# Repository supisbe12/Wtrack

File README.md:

# Wtrack
Wtrack — a multi-network location tracker device

Wtrack is a tracker with a combination of Apple Find My, Hubble (terrestrial + satellite), GPS, and BLE proximity detection on one barebones PCB (no enclosure) which goes inside your wallet.
I want it to be barebone because I wanted to be able to see the actual PCB because it looks cool ,But I am planning to add a layer acrylic spray that I already have available to prevent water from affecting the board.

---
Schematic

PCB

3D view

Battery Cap

---
Bill Of Materials: https://docs.google.com/spreadsheets/d/1D9NDHI8oiGVwoLBUYLz9mFe_7Vkk39w_oN8q6zxxxLU/edit?usp=sharing

Bill of materials (CSV): https://github.com/supisbe12/Wtrack/blob/main/BOM.csv

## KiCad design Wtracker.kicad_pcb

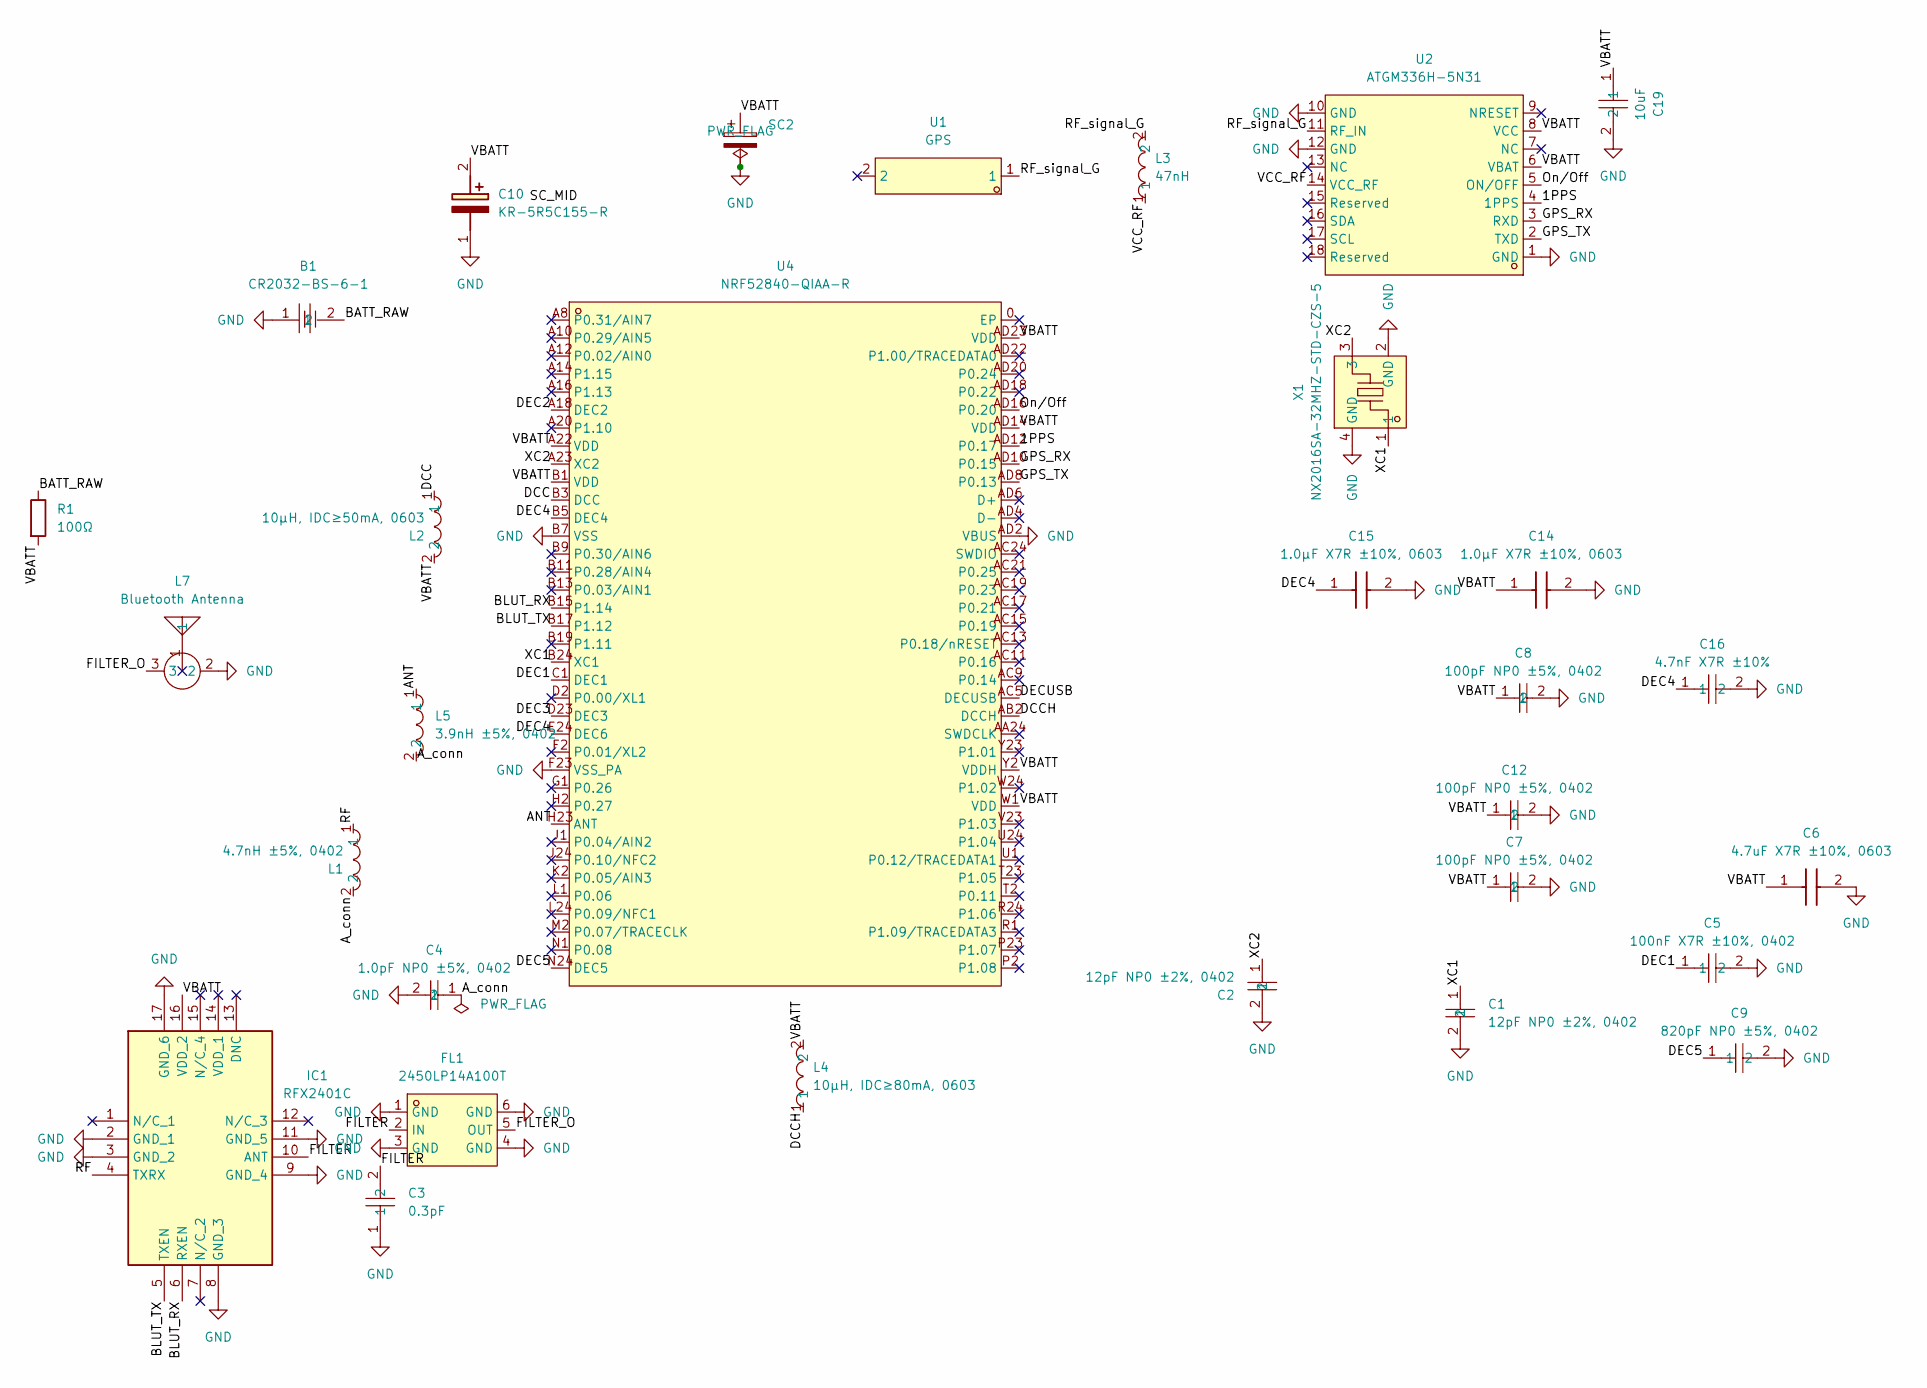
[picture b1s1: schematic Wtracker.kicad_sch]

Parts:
B1: CR2032-BS-6-1; BAT-TH_CR2032-BS-6-1; MPN CR2032-BS-6-1; LCSC Part C70377
C1, C2: 12pF NP0 ±2%, 0402; C0402; MPN 0402CG120J500NT; LCSC Part C1547
C3: 0.3pF; C0201; MPN GRM0335C1ER30BA01D; LCSC Part C88909
C4: 1.0pF NP0 ±5%, 0402; C0402; MPN 0402CG101J500NT; LCSC Part C1546
C5: 100nF X7R ±10%, 0402; C0402; MPN CL05B104KO5NNNC; LCSC Part C1525
C6: 4.7uF X7R ±10%, 0603; C_0603_1608Metric; Mouser Part Number 81-GRM188Z71A475KE5D
C7, C8, C12: 100pF NP0 ±5%, 0402; C0402; MPN 0402CG101J500NT; LCSC Part C1546
C9: 820pF NP0 ±5%, 0402; C0402; MPN CL05B104KO5NNNC; LCSC Part C1525
C10: KR-5R5C155-R; KR5R5C155R; Mouser Part Number 504-KR-5R5C155-R
C14, C15: 1.0µF X7R ±10%, 0603; C_0603_1608Metric; Mouser Part Number 81-GRM188Z71A475KE5D
C16: 4.7nF X7R ±10%; C0402; MPN CL05B104KO5NNNC; LCSC Part C1525
C19: 10uF; C0603; MPN CL10A106KP8NNNC; LCSC Part C19702
FL1: 2450LP14A100T; FILTER-SMD_0603-6P-L1.6-W0.8_2450LP14A100T; MPN 2450LP14A100T; LCSC Part C3155782
IC1: RFX2401C; QFN50P300X300X60-17N-D; Mouser Part Number 477-RFX2401C
L1: 4.7nH ±5%, 0402; L0402; MPN LQP15MN4N7B02D; LCSC Part C23769
L2: 10µH, IDC≥50mA, 0603; L0603; MPN SDFL1608S100KTF; LCSC Part C1035
L3: 47nH; L0402; MPN LQW15AN47NG00D; LCSC Part C22334
L4: 10µH, IDC≥80mA, 0603; L0603; MPN SDFL1608S100KTF; LCSC Part C1035
L5: 3.9nH ±5%, 0402; L0402; MPN LQG15HS2N2S02D; LCSC Part C86061
L7: Bluetooth Antenna; ANT-SMD_3P-L3.1-W1.6_ANT3216A063R2400A; MPN ANT3216A063R2400A; LCSC Part C412135
R1: 100Ω; R_0402_1005Metric
SC2: 3F,2.7V; CP_Radial_D10.0mm_P5.00mm
U1: GPS; ANT-SMD_L10.0-W3.0; MPN GPS1003; LCSC Part C239243
U2: ATGM336H-5N31; GPSM-SMD_ATGM336H-TR; MPN ATGM336H-5N31; LCSC Part C90770
U4: NRF52840-QIAA-R; AQFN-73_L7.0-W7.0-P0.50-BL-EP4.8; MPN NRF52840-QIAA-R; LCSC Part C190794
X1: NX2016SA-32MHZ-STD-CZS-5; OSC-SMD_4P-L2.0-W1.6-BL; MPN NX2016SA-32MHZ-STD-CZS-5; LCSC Part C843260

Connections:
/1PPS: U2.4 (1PPS), U4.AD12 (P0.17)
/ANT: L5.1, U4.H23 (ANT)
/A_conn: C4.1, L1.2, L5.2
/BATT_RAW: B1.2, R1.1
/BLUT_RX: IC1.6 (RXEN), U4.B15 (P1.14)
/BLUT_TX: IC1.5 (TXEN), U4.B17 (P1.12)
/DCC: L2.1, U4.B3 (DCC)
/DCCH: L4.1, U4.AB2 (DCCH)
/DEC1: C5.1, U4.C1 (DEC1)
/DEC2: U4.A18 (DEC2)
/DEC3: U4.D23 (DEC3)
/DEC4: C15.1, C16.1, U4.B5 (DEC4), U4.E24 (DEC6)
/DEC5: C9.1, U4.N24 (DEC5)
/DECUSB: U4.AC5 (DECUSB)
/FILTER: C3.2, FL1.2 (IN), IC1.10 (ANT)
/FILTER_O: FL1.5 (OUT), L7.3
/GPS_RX: U2.3 (RXD), U4.AD10 (P0.15)
/GPS_TX: U2.2 (TXD), U4.AD8 (P0.13)
/On/Off: U2.5 (ON/OFF), U4.AD16 (P0.20)
/RF: IC1.4 (TXRX), L1.1
/RF_signal_G: L3.2, U1.1 (1_1), U2.11 (RF_IN)
/VBATT: C6.1, C7.1, C8.1, C10.2 (+), C12.1, C14.1, C19.1, IC1.16 (VDD_2), L2.2, L4.2, R1.2, SC2.1, U2.6 (VBAT), U2.8 (VCC), U4.A22 (VDD), U4.AD14 (VDD), U4.AD23 (VDD), U4.B1 (VDD), U4.W1 (VDD), U4.Y2 (VDDH)
/VCC_RF: L3.1, U2.14 (VCC_RF)
/XC1: C1.1, U4.B24 (XC1), X1.1
/XC2: C2.1, U4.A23 (XC2), X1.3
GND: B1.1, C1.2, C2.2, C3.1, C4.2, C5.2, C6.2, C7.2, C8.2, C9.2, C10.1 (-), C12.2, C14.2, C15.2, C16.2, C19.2, FL1.1 (GND), FL1.3 (GND), FL1.4 (GND), FL1.6 (GND), IC1.2 (GND_1), IC1.3 (GND_2), IC1.8 (GND_3), IC1.9 (GND_4), IC1.11 (GND_5), IC1.17 (GND_6), L7.2, SC2.2, U2.1 (GND), U2.10 (GND), U2.12 (GND), U4.AD2 (VBUS), U4.B7 (VSS), U4.F23 (VSS_PA), X1.2 (GND), X1.4 (GND)

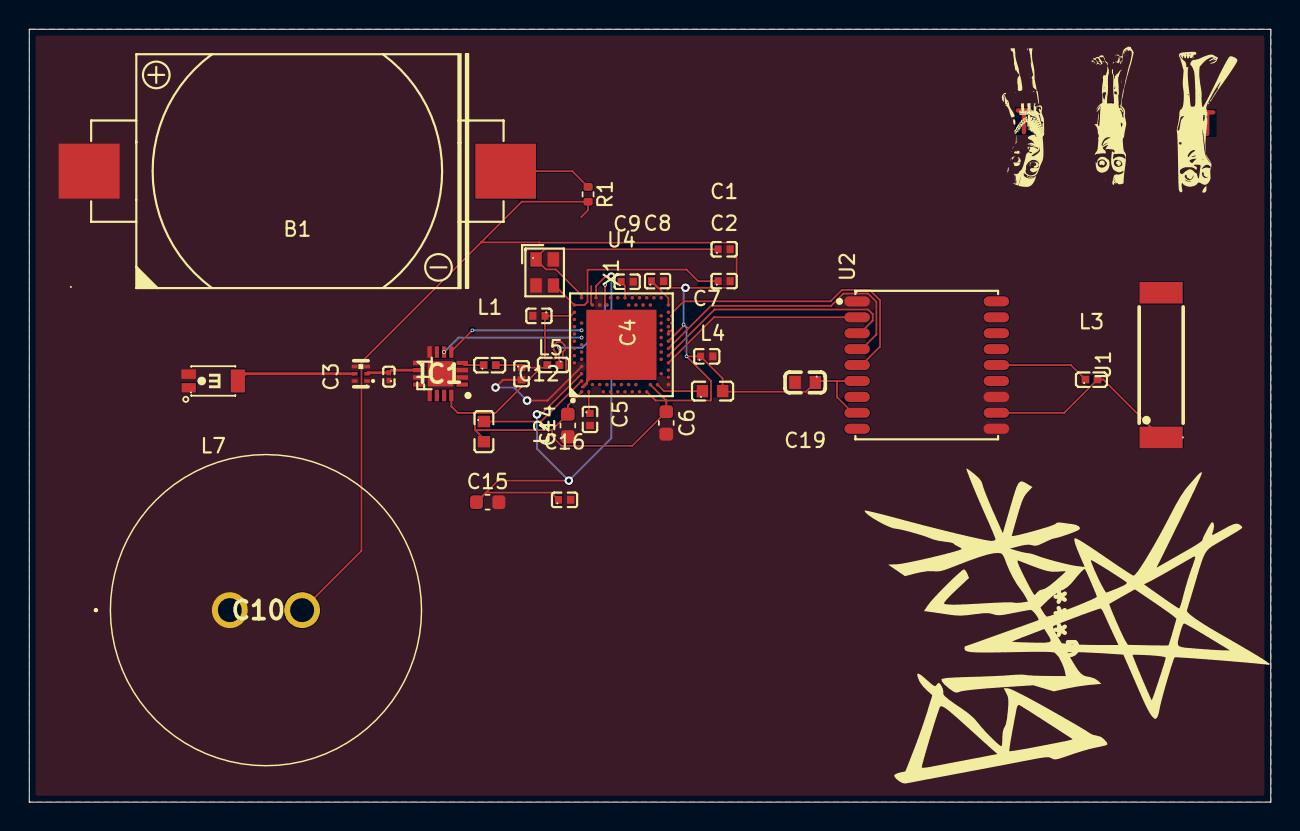
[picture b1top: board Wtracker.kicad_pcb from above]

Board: 2 copper layers, 85.8 x 53.4 mm, 32 parts (0 on the bottom side), 23 nets.

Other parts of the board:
T: LOGO
T#2, T#3: LOGO
